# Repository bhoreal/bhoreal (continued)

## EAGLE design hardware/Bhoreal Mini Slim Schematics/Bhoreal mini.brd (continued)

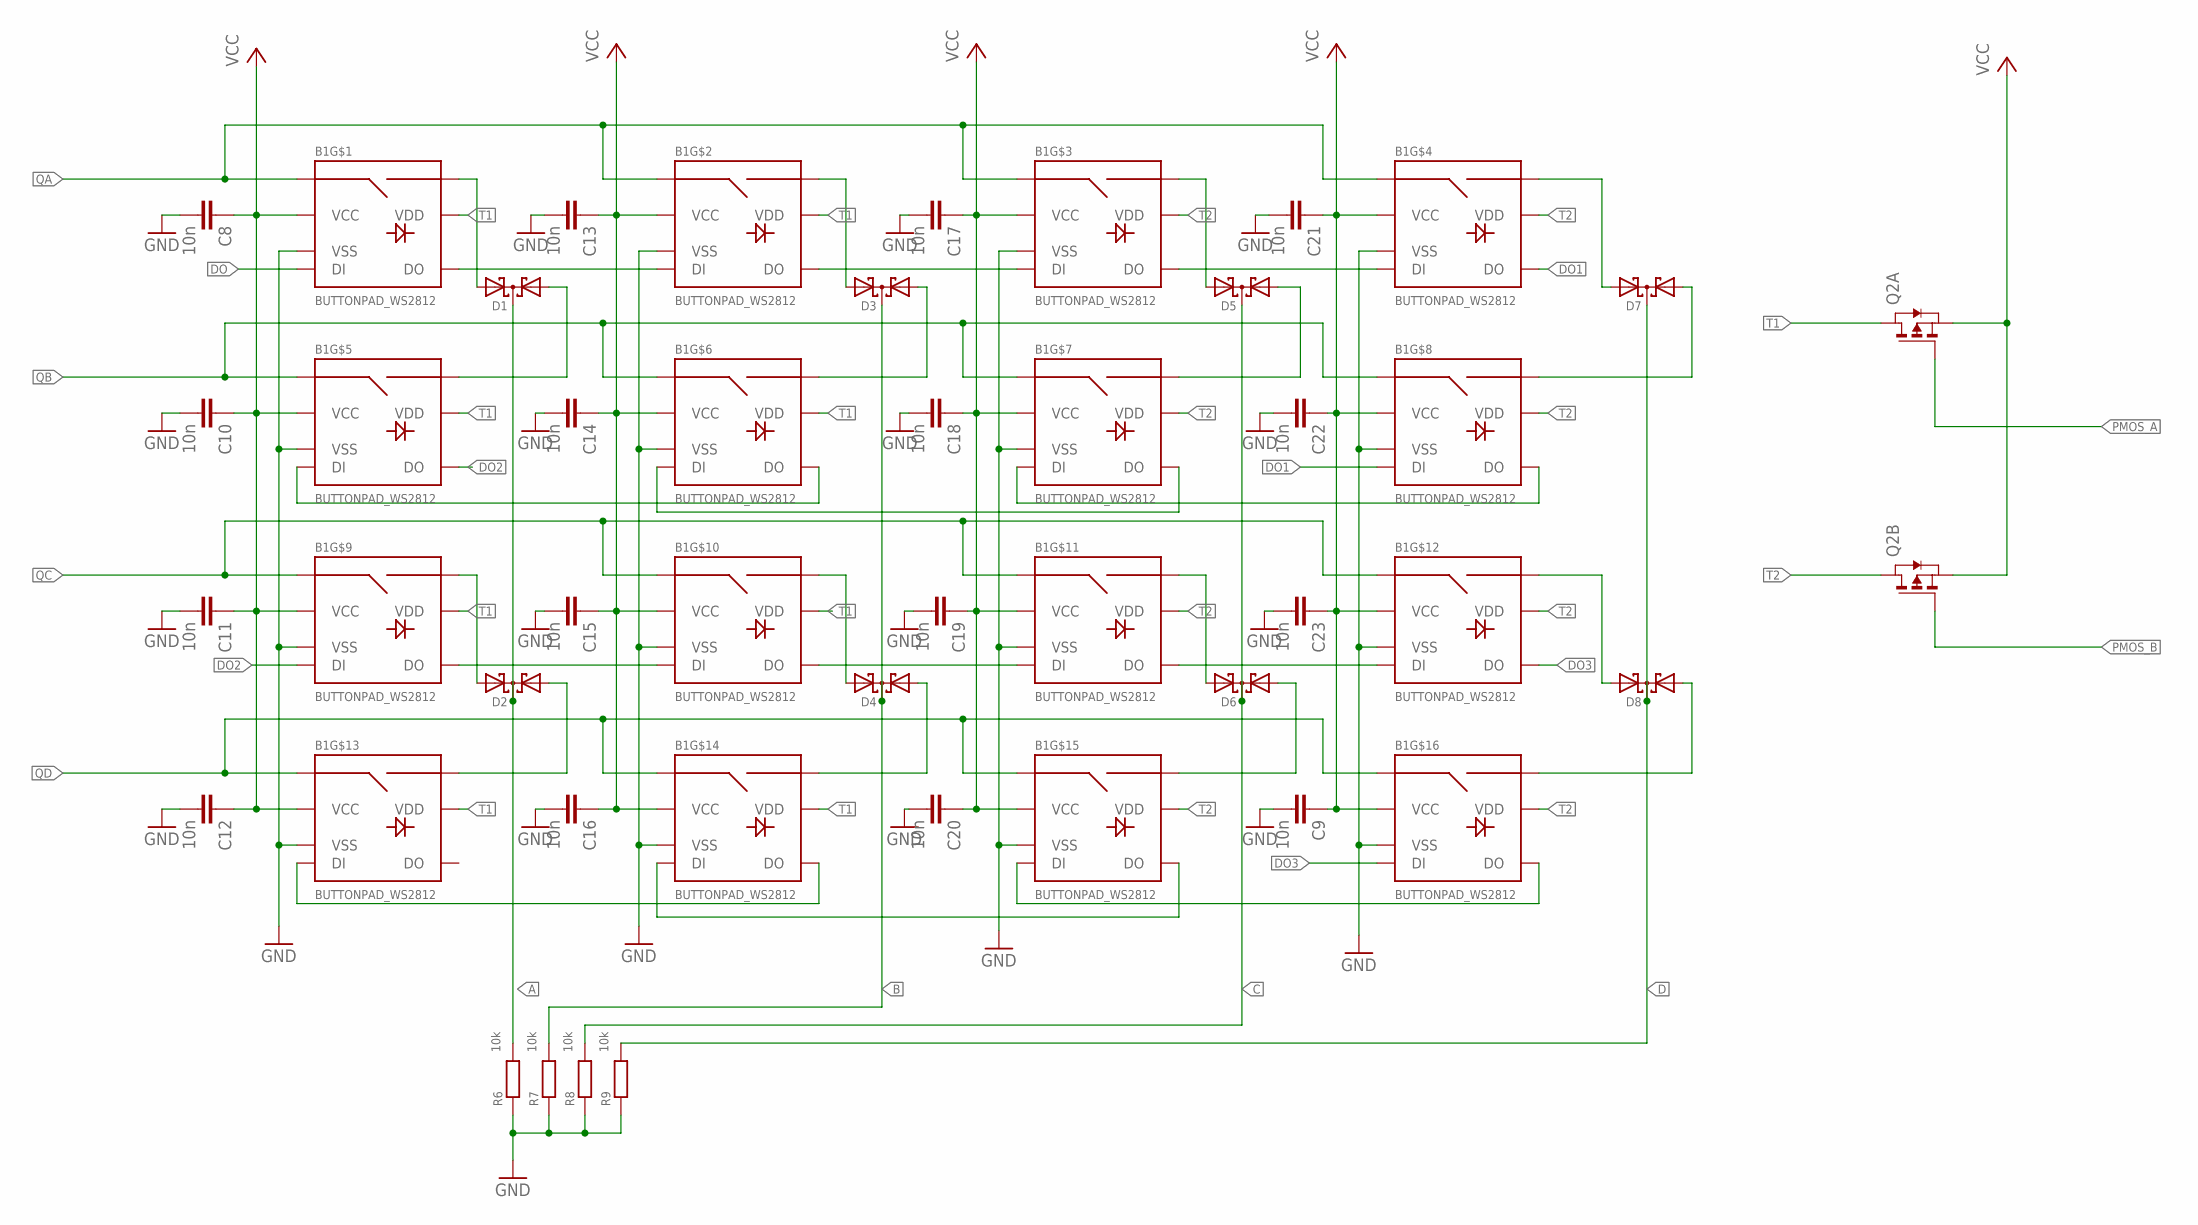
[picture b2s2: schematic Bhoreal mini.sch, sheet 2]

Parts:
B1: BUTTONPAD_WS2812
C8, C9, C10, C11, C12, C13, C14, C15, C16, C17, C18, C19, C20, C21, C22, C23: 10n; C0603
D1, D2, D3, D4, D5, D6, D7, D8: BAS70-05; SOT23
Q2: PMOS2SO8; SO8
R6, R7, R8, R9: 10k; R0603

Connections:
A: D1.3 (C), D2.3 (C), R6.2; also elsewhere on the board
B: D3.3 (C), D4.3 (C), R7.2; also elsewhere on the board
C: D5.3 (C), D6.3 (C), R8.2; also elsewhere on the board
D: D7.3 (C), D8.3 (C), R9.2; also elsewhere on the board
DO: B1.2A (DI); also elsewhere on the board
DO1: B1.1D (DO), B1.2H (DI)
DO2: B1.1E (DO), B1.2I (DI)
DO3: B1.1L (DO), B1.2P (DI)
GND: B1.6A (VSS), B1.6B (VSS), B1.6C (VSS), B1.6D (VSS), B1.6E (VSS), B1.6F (VSS), B1.6G (VSS), B1.6H (VSS), B1.6I (VSS), B1.6J (VSS), B1.6K (VSS), B1.6L (VSS), B1.6M (VSS), B1.6N (VSS), B1.6O (VSS), B1.6P (VSS), C8.2, C9.2, C10.2, C11.2, C12.2, C13.2, C14.2, C15.2, C16.2, C17.2, C18.2, C19.2, C20.2, C21.2, C22.2, C23.2, R6.1, R7.1, R8.1, R9.1; also elsewhere on the board
unnamed: B1.SIG2A (SIG2), D1.2 (A2)
unnamed: B1.SIG2E (SIG2), D1.1 (A1)
unnamed: B1.SIG2I (SIG2), D2.2 (A2)
unnamed: B1.SIG2M (SIG2), D2.1 (A1)
unnamed: B1.SIG2B (SIG2), D3.2 (A2)
unnamed: B1.SIG2F (SIG2), D3.1 (A1)
unnamed: B1.SIG2J (SIG2), D4.2 (A2)
unnamed: B1.SIG2N (SIG2), D4.1 (A1)
unnamed: B1.SIG2C (SIG2), D5.2 (A2)
unnamed: B1.SIG2G (SIG2), D5.1 (A1)
unnamed: B1.SIG2K (SIG2), D6.2 (A2)
unnamed: B1.SIG2O (SIG2), D6.1 (A1)
unnamed: B1.SIG2L (SIG2), D8.2 (A2)
unnamed: B1.SIG2P (SIG2), D8.1 (A1)
unnamed: B1.SIG2D (SIG2), D7.2 (A2)
unnamed: B1.SIG2H (SIG2), D7.1 (A1)
unnamed: B1.1A (DO), B1.2B (DI)
unnamed: B1.1F (DO), B1.2E (DI)
unnamed: B1.1G (DO), B1.2F (DI)
unnamed: B1.1B (DO), B1.2C (DI)
unnamed: B1.1C (DO), B1.2D (DI)
unnamed: B1.1H (DO), B1.2G (DI)
unnamed: B1.1K (DO), B1.2L (DI)
unnamed: B1.1J (DO), B1.2K (DI)
unnamed: B1.1I (DO), B1.2J (DI)
unnamed: B1.1P (DO), B1.2O (DI)
unnamed: B1.1O (DO), B1.2N (DI)
unnamed: B1.1N (DO), B1.2M (DI)
PMOS_A: Q2.2 (G); also elsewhere on the board
PMOS_B: Q2.4 (G); also elsewhere on the board
QA: B1.SIG1A (SIG1), B1.SIG1B (SIG1), B1.SIG1C (SIG1), B1.SIG1D (SIG1); also elsewhere on the board
QB: B1.SIG1E (SIG1), B1.SIG1F (SIG1), B1.SIG1G (SIG1), B1.SIG1H (SIG1); also elsewhere on the board
QC: B1.SIG1I (SIG1), B1.SIG1J (SIG1), B1.SIG1K (SIG1), B1.SIG1L (SIG1); also elsewhere on the board
QD: B1.SIG1M (SIG1), B1.SIG1N (SIG1), B1.SIG1O (SIG1), B1.SIG1P (SIG1); also elsewhere on the board
T1: B1.5A (VDD), B1.5B (VDD), B1.5E (VDD), B1.5F (VDD), B1.5I (VDD), B1.5J (VDD), B1.5M (VDD), B1.5N (VDD), Q2.7 (D), Q2.8 (D)
T2: B1.5C (VDD), B1.5D (VDD), B1.5G (VDD), B1.5H (VDD), B1.5K (VDD), B1.5L (VDD), B1.5O (VDD), B1.5P (VDD), Q2.5 (D), Q2.6 (D)
VCC: B1.3A (VCC), B1.3B (VCC), B1.3C (VCC), B1.3D (VCC), B1.3E (VCC), B1.3F (VCC), B1.3G (VCC), B1.3H (VCC), B1.3I (VCC), B1.3J (VCC), B1.3K (VCC), B1.3L (VCC), B1.3M (VCC), B1.3N (VCC), B1.3O (VCC), B1.3P (VCC), C8.1, C9.1, C10.1, C11.1, C12.1, C13.1, C14.1, C15.1, C16.1, C17.1, C18.1, C19.1, C20.1, C21.1, C22.1, C23.1, Q2.1 (S), Q2.3 (S); also elsewhere on the board

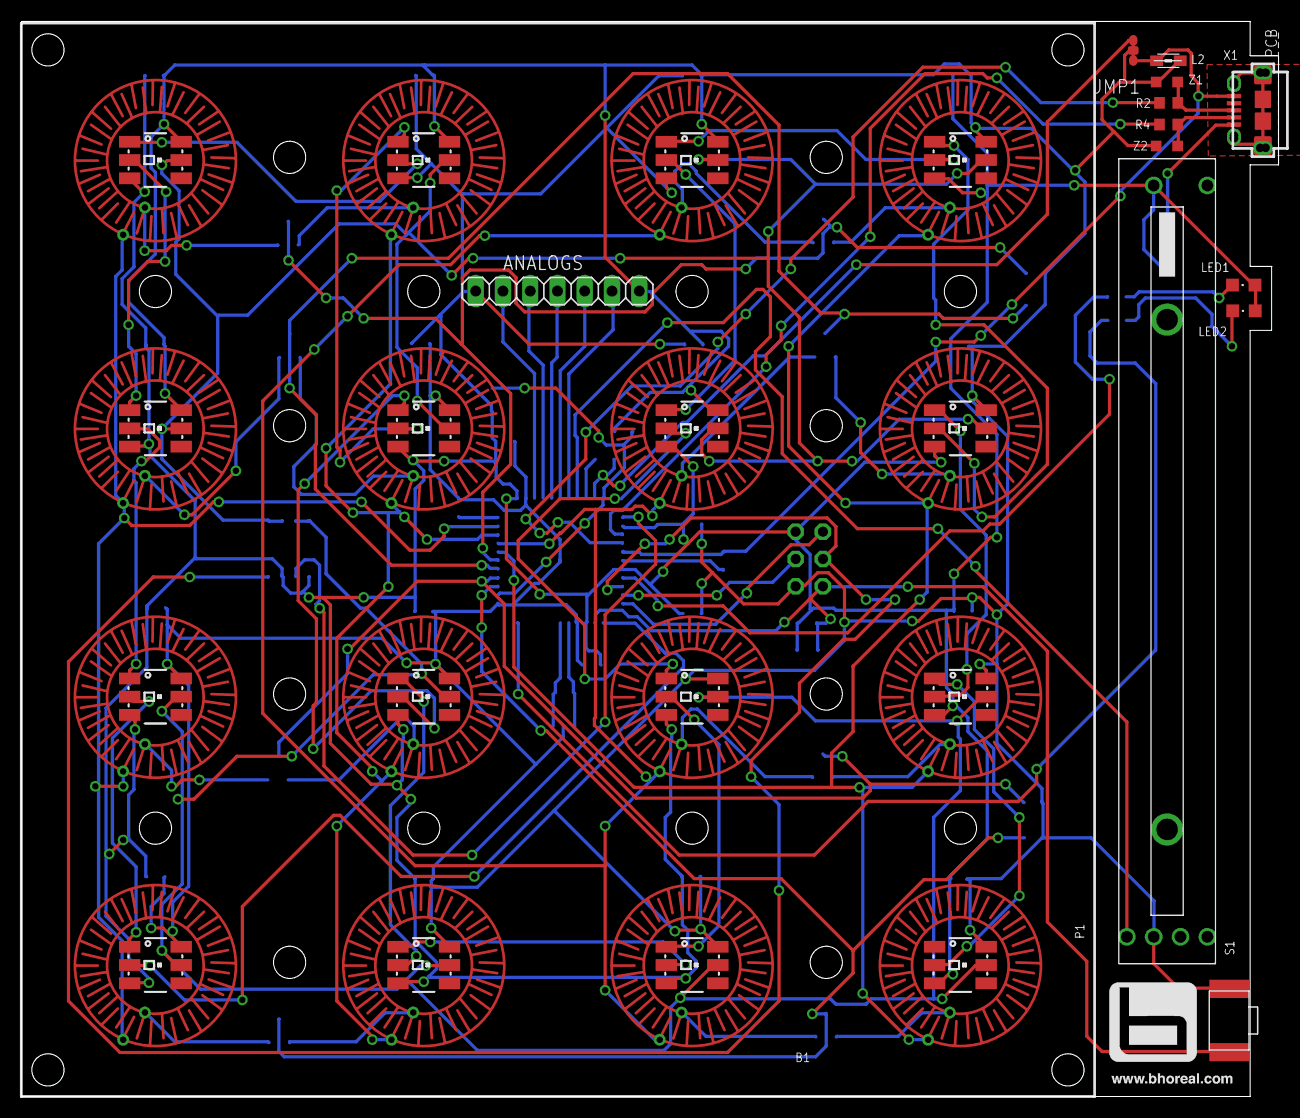
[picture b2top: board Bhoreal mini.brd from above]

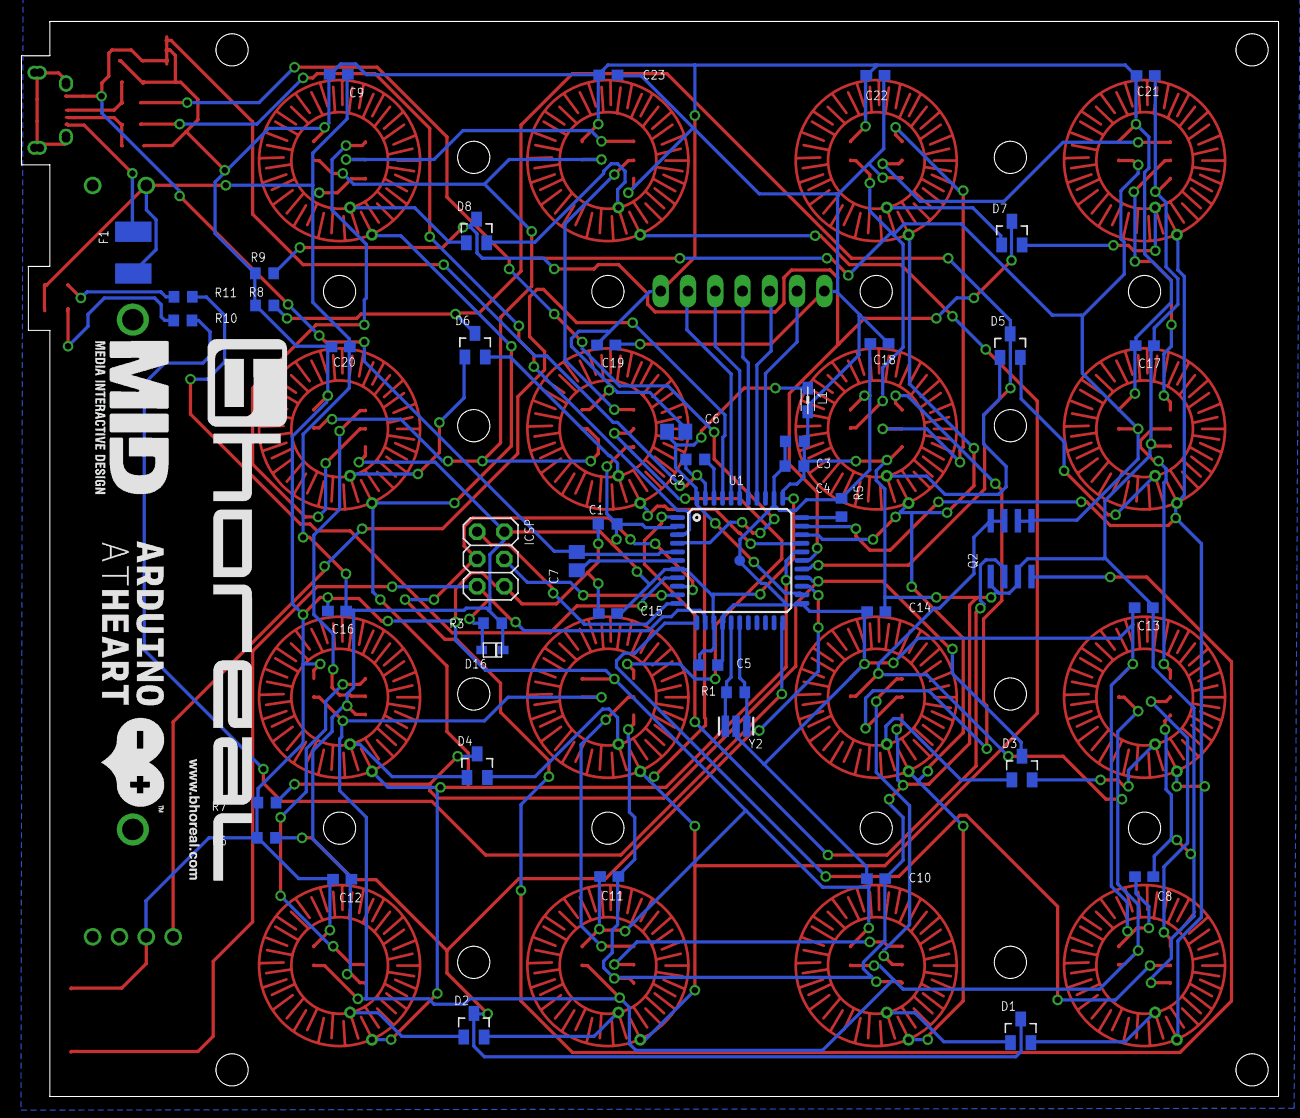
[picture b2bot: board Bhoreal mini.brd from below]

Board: 2 copper layers, 117.1 x 100.2 mm, 60 parts (47 on the bottom side), 72 nets.

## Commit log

2014-05-04 Create images
2014-05-05 commit again
2014-05-05 image change
2014-05-05 modificando readme.md
2014-05-06 Añadimos otra linea
2014-05-06 y otra más más más
2014-05-06 y otra
2014-05-06 Remove images directory
2014-05-07 Adding firmware
2014-05-07 gitignore
2014-05-07 README.md file modified
2017-06-12 "test app" (MIDI test in MAX)
2017-06-12 Windows7 Bhoreal Driver
    The required driver to connect Windows with Bhoreal.
2017-06-22 Processing Bhoreal Emulator
    Emulation of Bhoreal SLIM model, where you can see the OSC communication
2017-06-22 Create ti
2017-06-22 Create t
2017-06-22 Processing Bhoreal Emulator
    Emulation of Bhoreal in Processing, where you can see the OSC communication
2017-06-28 Bhoreal LED test
    A patch from MAX where you can select a Bhoreal pad and change its color
2017-07-10 Rename software/MAX/Bhoreal_MIDI-OSC_com.maxpat to software/MAX/MIDI-OSC_Router/Bhoreal_MIDI-OSC_com.maxpat
2017-07-11 Rename software/PureData/Bhoral_MIDI-OSC_comm.pd to software/PureData/MIDI-OSC_Router/Bhoreal_MIDI-OSC_comm.pd
2017-07-11 Rename software/PureData/MIDI-OSC_Router/Bhoreal_MIDI-OSC_comm.pd to software/PureData/MIDI-OSC_RouterBhoreal_MIDI-OSC_comm.pd
